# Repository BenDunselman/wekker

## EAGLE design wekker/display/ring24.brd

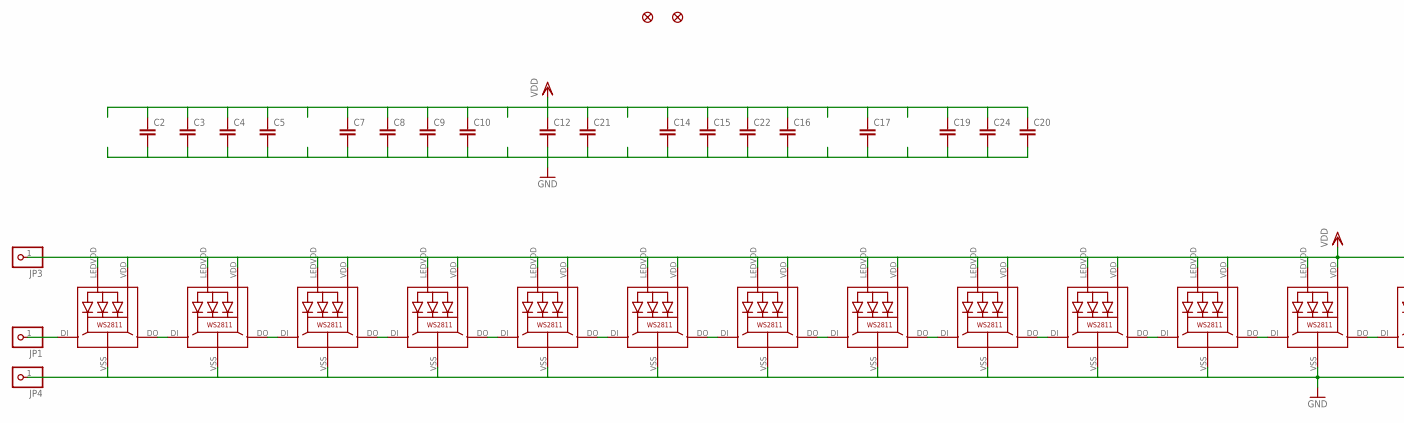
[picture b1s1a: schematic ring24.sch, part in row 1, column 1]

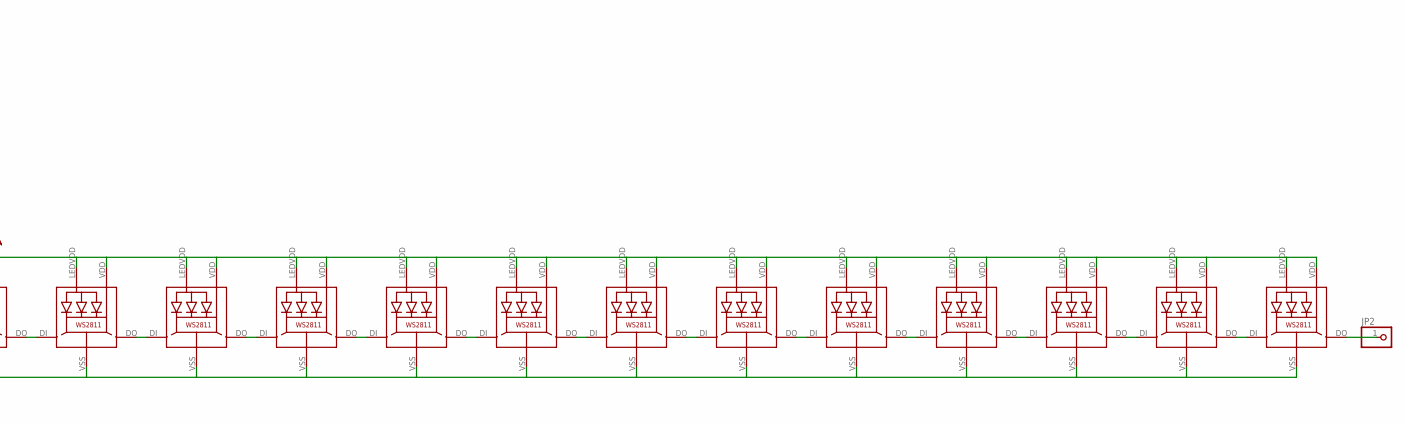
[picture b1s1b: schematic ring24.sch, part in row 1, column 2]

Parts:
C2, C3, C4, C5, C7, C8, C9, C10, C12, C14, C15, C16, C17, C19, C20, C21, C22, C24: C-EUC0603; C0603
FID1, FID2: FIDUCIAL""; FIDUCIAL_1MM
JP1, JP2, JP3, JP4: PINHD-1X1CB; 1X01-CLEANBIG
LED1, LED2, LED3, LED4, LED5, LED6, LED7, LED8, LED9, LED10, LED11, LED12, LED13, LED14, LED15, LED16, LED17, LED18, LED19, LED20, LED21, LED22, LED23, LED24: WS28115050

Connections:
GND: C2.2, C3.2, C4.2, C5.2, C7.2, C8.2, C9.2, C10.2, C12.2, C14.2, C15.2, C16.2, C17.2, C19.2, C20.2, C21.2, C22.2, C24.2, JP4.1, LED1.VSS (GND), LED2.VSS (GND), LED3.VSS (GND), LED4.VSS (GND), LED5.VSS (GND), LED6.VSS (GND), LED7.VSS (GND), LED8.VSS (GND), LED9.VSS (GND), LED10.VSS (GND), LED11.VSS (GND), LED12.VSS (GND), LED13.VSS (GND), LED14.VSS (GND), LED15.VSS (GND), LED16.VSS (GND), LED17.VSS (GND), LED18.VSS (GND), LED19.VSS (GND), LED20.VSS (GND), LED21.VSS (GND), LED22.VSS (GND), LED23.VSS (GND), LED24.VSS (GND)
unnamed: LED1.DO, LED2.DI
unnamed: LED2.DO, LED3.DI
unnamed: LED3.DO, LED4.DI
unnamed: LED4.DO, LED5.DI
unnamed: LED5.DO, LED6.DI
unnamed: LED6.DO, LED7.DI
unnamed: LED7.DO, LED8.DI
unnamed: LED8.DO, LED9.DI
unnamed: LED9.DO, LED10.DI
unnamed: LED10.DO, LED11.DI
unnamed: LED11.DO, LED12.DI
unnamed: LED12.DO, LED13.DI
unnamed: LED13.DO, LED14.DI
unnamed: LED14.DO, LED15.DI
unnamed: LED15.DO, LED16.DI
unnamed: LED16.DO, LED17.DI
unnamed: LED17.DO, LED18.DI
unnamed: LED18.DO, LED19.DI
unnamed: LED19.DO, LED20.DI
unnamed: LED20.DO, LED21.DI
unnamed: LED21.DO, LED22.DI
unnamed: LED22.DO, LED23.DI
unnamed: LED23.DO, LED24.DI
unnamed: JP2.1, LED24.DO
unnamed: JP1.1, LED1.DI
VDD: C2.1, C3.1, C4.1, C5.1, C7.1, C8.1, C9.1, C10.1, C12.1, C14.1, C15.1, C16.1, C17.1, C19.1, C20.1, C21.1, C22.1, C24.1, JP3.1, LED1.LEDVDD, LED1.VDD, LED2.LEDVDD, LED2.VDD, LED3.LEDVDD, LED3.VDD, LED4.LEDVDD, LED4.VDD, LED5.LEDVDD, LED5.VDD, LED6.LEDVDD, LED6.VDD, LED7.LEDVDD, LED7.VDD, LED8.LEDVDD, LED8.VDD, LED9.LEDVDD, LED9.VDD, LED10.LEDVDD, LED10.VDD, LED11.LEDVDD, LED11.VDD, LED12.LEDVDD, LED12.VDD, LED13.LEDVDD, LED13.VDD, LED14.LEDVDD, LED14.VDD, LED15.LEDVDD, LED15.VDD, LED16.LEDVDD, LED16.VDD, LED17.LEDVDD, LED17.VDD, LED18.LEDVDD, LED18.VDD, LED19.LEDVDD, LED19.VDD, LED20.LEDVDD, LED20.VDD, LED21.LEDVDD, LED21.VDD, LED22.LEDVDD, LED22.VDD, LED23.LEDVDD, LED23.VDD, LED24.LEDVDD, LED24.VDD

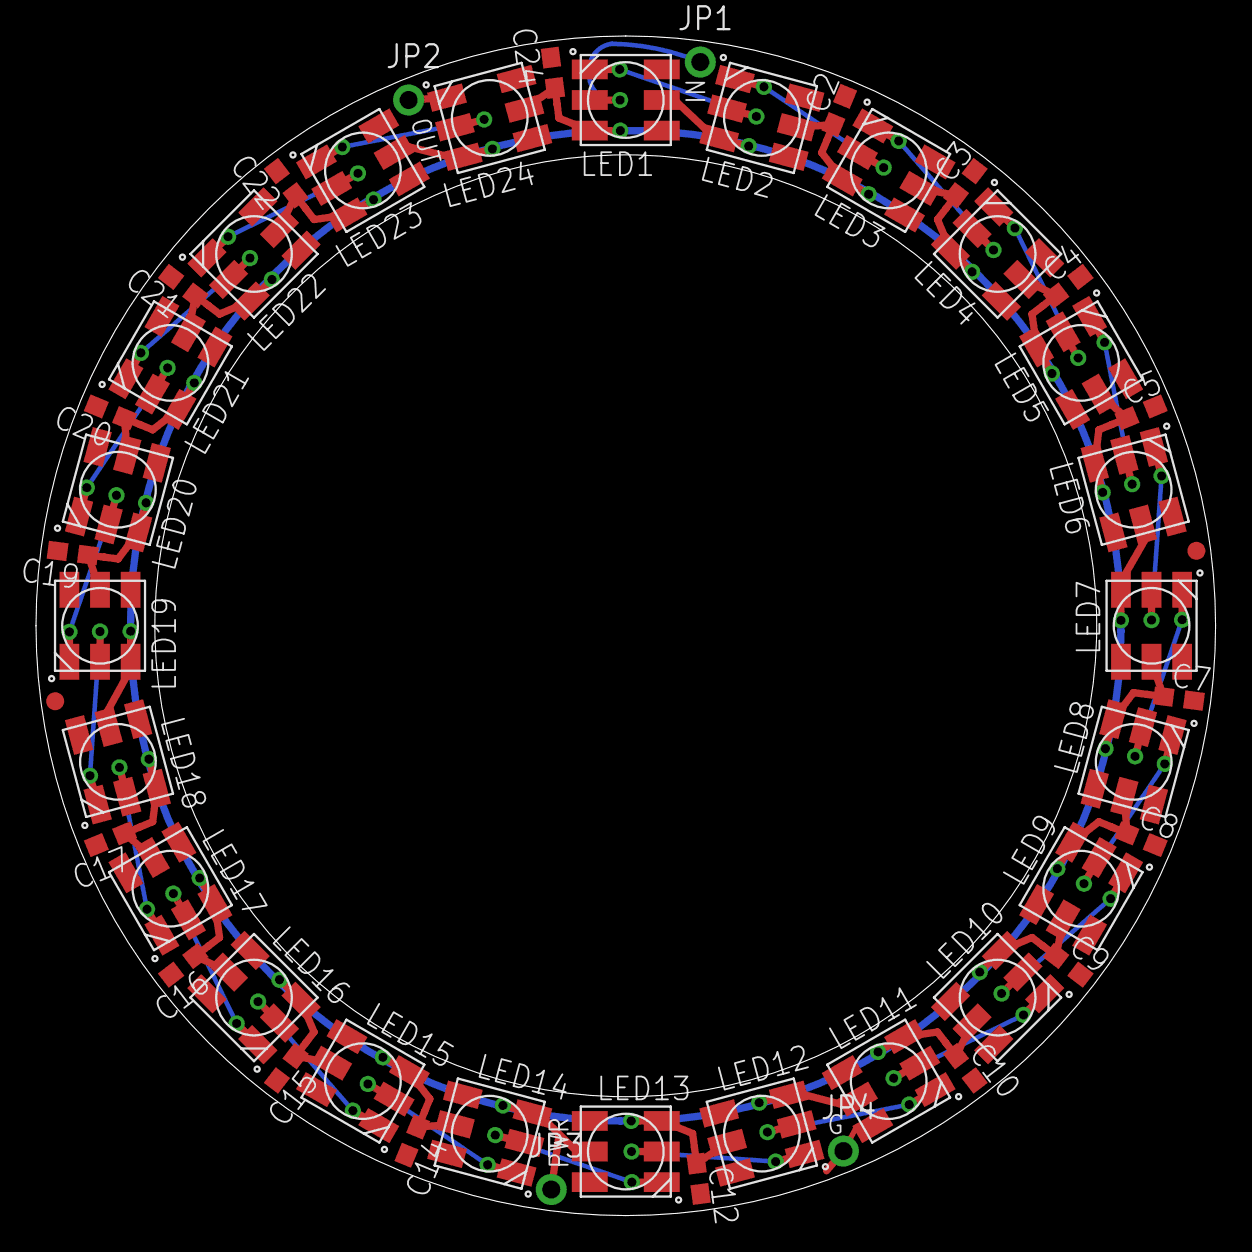
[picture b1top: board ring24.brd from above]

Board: 2 copper layers, 65.5 x 65.5 mm, 49 parts (1 on the bottom side), 27 nets.

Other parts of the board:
U$1: ADAFRUIT_5MM

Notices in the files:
parts and their libraries:
microbuilder: This work is placed in the public domain, and may be freely used for commercial and non-commercial work with the following conditions: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
